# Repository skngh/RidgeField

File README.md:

# Ridge Field

Fully wireless guitar pedal. A small box mounts on the guitar and sends its knobs, joystick and light sensor over Bluetooth to the pedal on the floor, which runs everything and does processing through a Daisy Seed.

**[Full video walking through the pedal!](https://youtu.be/8Uf5aeJEN9k)**

Everything here is free to use!! Please let me know if you make anything with something here, I'd really love to see :)

## Contents

- [`hardware/`](hardware/): KiCad projects for both boards, custom libraries, and ready-to-order PCBWay files
- [`firmware/`](firmware/): all the code
  - [`firmware/daisy/`](firmware/daisy/): the audio DSP running on the Daisy Seed in the pedal
  - [`firmware/ESP32C3/`](firmware/ESP32C3/): the Bluetooth link (guitar-side server and pedal-side client)
- [`enclosure/`](enclosure/): FreeCAD models, STLs, and the Tayda drill template

## How it works

There are two units:

- **Server (on the guitar):** a XIAO ESP32-C3 reads the two knobs, an LDR (light sensor) and a joystick, then sends any changes over BLE. It runs off a Li-ion battery.
- **Main/Client (the pedal):** a second XIAO ESP32-C3 connects to the server and passes the control values to a Daisy Seed over UART. Then the Daisy does all the audio processing.

## Controls

| Control            | What it does                                                             |
| ------------------ | ------------------------------------------------------------------------ |
| Knob 1             | Delay time                                                               |
| Knob 2             | Delay feedback (fully down turns the delay off)                          |
| LDR                | Reverb. Cover it with your hand for more                                 |
| Joystick X         | Pitch shift, an octave up or down depending on direction                 |
| Joystick Y         | Bitcrusher. One direction lowers bit depth, the other lowers sample rate |
| Button press       | Latch the current joystick position                                      |
| Button hold        | LDR calibration, see below                                               |
| Mix knob (pedal)   | Dry/wet                                                                  |
| Footswitch (pedal) | Bypass                                                                   |

**LDR calibration:** hold the joystick button. For the first few seconds leave the LDR uncovered. Once the LED starts blinking fast, cover it and keep holding until the LED goes back to normal (~7 s total). The pedal saves the calibration so it survives next time you unplug and replug.

## Building one

Rough order:

1. **PCBs:** order the 2 pcbs located in [`hardware/PCBWayFiles`](hardware/PCBWayFiles/) (Gerbers, BOM and pick-and-place are all there).
2. **Server Enclosure:** 3D print the parts in [`enclosure/STL files`](enclosure/STL%20files/). Uses [M3x6mm screws](https://www.amazon.com/dp/B0DJQG5YLF?ref_=ppx_hzsearch_conn_dt_b_fed_asin_title_2) and [M3 heat inserts](https://www.amazon.com/dp/B08BCRZZS3).
3. **Main Enclosure:** the main enclosure is a 1590B pedal. I used [Tayda Electronics](https://www.taydaelectronics.com/1590b-style-aluminum-diecast-enclosure.html) for mine so I could order it fully drilled and with a UV print. Here's the [Tayda drill template](enclosure/Tayda_Drill_Schematic.txt).
4. **Firmware:** flash both ESP32-C3s from [`firmware/ESP32C3`](firmware/ESP32C3/), then build and flash the Daisy from [`firmware/daisy`](firmware/daisy/).

See each folder's README for more details.

## The artwork

I got the art on the enclosure UV printed through Tayda. The art isn't included in this repo, but here's how I did it in Blender!

You can attach an image as a background to a camera in Blender. So I took the drill schematic coords and made an illustrator file showing the holes that I added as the background. Then I could easily place objects in the scene and it would line up later with the pedal (for some reason the bluetooth LED on the left didn't line up perfectly, so I think I must've gotten the coords off a tiny bit).

I have a video [here](https://www.youtube.com/watch?v=Ckmy4d0Q_N0&t=555s) showing how to make designs for Tayda's UV printing service.

## Clone it

The DSP library I used is a git submodule, so clone with:

```sh
git clone --recursive https://github.com/skngh/RidgeField.git
# if you already cloned it:
git submodule update --init
```

## Caveats

As I mentioned in the video, I am actually planning on making a V2 of the main pedal PCB going forward. It is fully functioning, but you can hear some of the data transfers as these consistent beeps going, and I'm an idiot who didn't add a LPF to the output buffer, so there's lots of high frequency noise. It's far above the range of human hearing, but I had this issue in the past where some annoying looper pedal folded that range down and caused all this aliasing (at least I think that's what happened), so I plan on making the board 4 layers and then adding a LPF across the output buffer's op amp. Relatively easy, but in order to test I'd have to reorder the boards and I don't really wanna spend that money right now :o

## Built with

- [Daisy Seed](https://electro-smith.com/products/daisy-seed) + [libDaisy](https://github.com/electro-smith/libDaisy) / [DaisySP](https://github.com/electro-smith/DaisySP)
- [Seeed XIAO ESP32-C3](https://wiki.seeedstudio.com/XIAO_ESP32C3_Getting_Started/)
- [NimBLE-Arduino](https://github.com/h2zero/NimBLE-Arduino)
- My [Simple-DSP](https://github.com/skngh/Simple-DSP) library
- KiCad 10.0, FreeCAD 1.1, Blender

## License

[MIT](LICENSE). Do whatever you want with it!

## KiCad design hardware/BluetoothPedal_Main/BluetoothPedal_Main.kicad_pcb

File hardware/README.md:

# Hardware

Made with **KiCad 10.0**. Older versions won't open these files.

- [`BluetoothPedal_Main/`](BluetoothPedal_Main/): the main pedal board. Includes the Daisy, XIAO ESP32-C3, input/output buffers, DC power, footswitch and mix knob.
- [`BluetoothPedal_Server/`](BluetoothPedal_Server/): the guitar-mounted board. XIAO ESP32-C3, MCP3208 ADC, knobs, LDR, joystick, battery.
- [`libs/`](libs/): custom symbols, footprints and 3D models used by both projects
- [`PCBWayFiles/`](PCBWayFiles/): Gerbers, BOM and pick-and-place (`-all-pos.csv`) for each board. If you just want boards, these are all you need.

## Opening the projects

I think both projects should open and look right without any setup? But if you want to edit or update parts you may need to do these steps below:

- **Footprints:** each project has an `fp-lib-table` pointing to `../libs/footprints/Custom_Footprints.pretty`. This originally was an absolute path that I changed, but I'm not totally positive that works so you may need to change it, idk.
- **Symbols:** `custom_symbols` and `Seeed_Studio_XIAO_Series` aren't registered in a project symbol table. If you need them, add `libs/symbols/*.kicad_sym` under _Preferences → Manage Symbol Libraries → Project Specific Libraries_.
- **3D models:** some models seem to be absolute paths from my computer, so you may need to configure them in each footprint's settings.

None of this affects the Gerbers, those should all work fine.

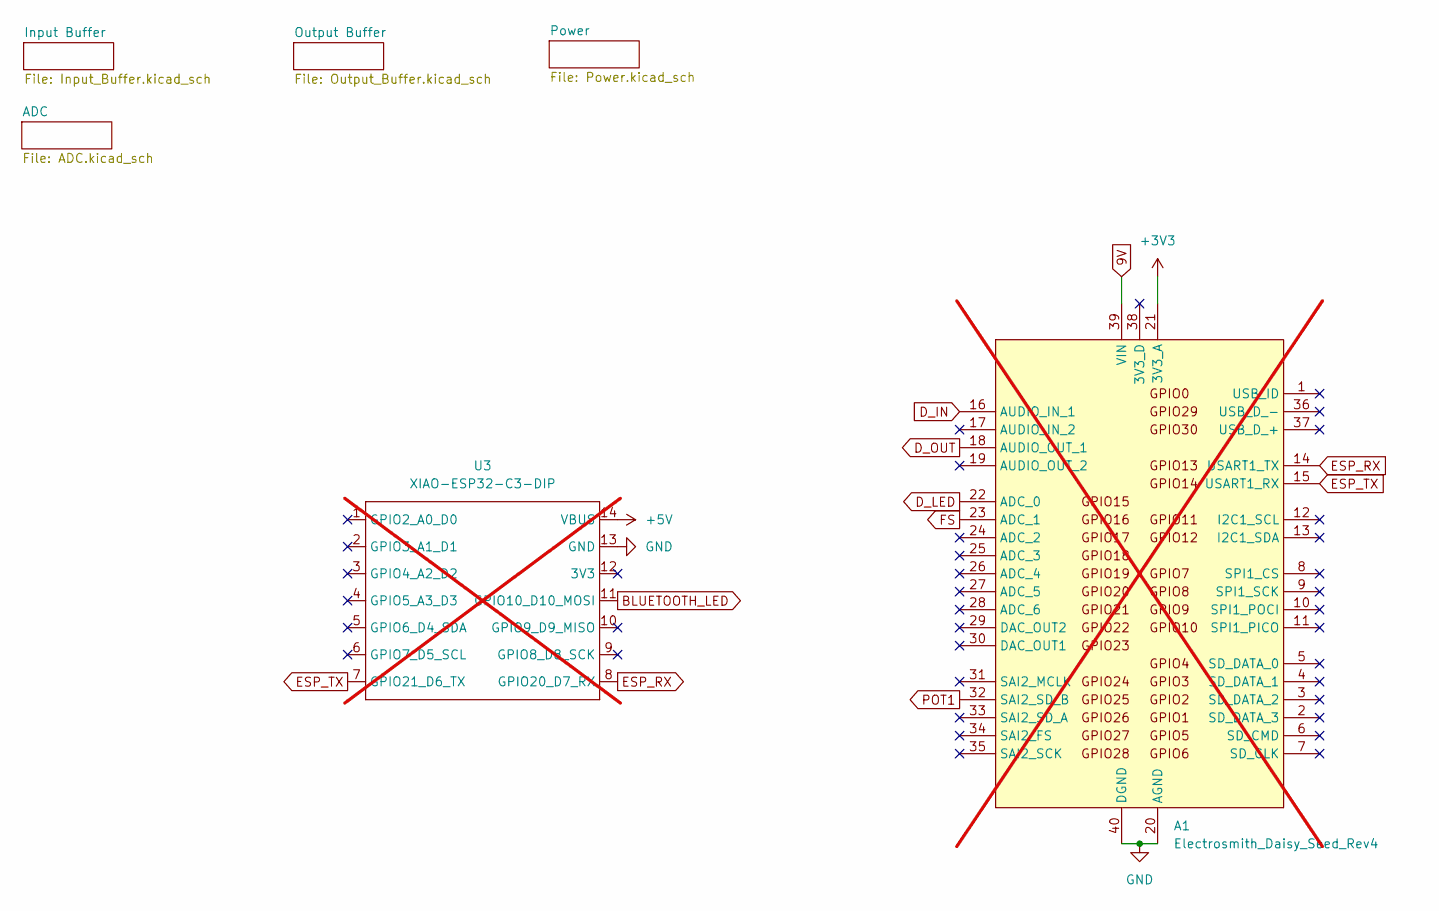
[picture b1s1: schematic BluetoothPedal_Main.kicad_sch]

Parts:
A1: Electrosmith_Daisy_Seed_Rev4; Electrosmith_Daisy_Seed; not fitted
U3: XIAO-ESP32-C3-DIP; not fitted

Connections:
9V: A1.39 (VIN); also elsewhere on the board
+3V3: A1.21 (3V3_A); also elsewhere on the board
+5V: U3.14 (VBUS); also elsewhere on the board
BLUETOOTH_LED: U3.11 (GPIO10_D10_MOSI); also elsewhere on the board
D_IN: A1.16 (AUDIO_IN_1); also elsewhere on the board
D_LED: A1.22 (ADC_0); also elsewhere on the board
D_OUT: A1.18 (AUDIO_OUT_1); also elsewhere on the board
ESP_RX: A1.14 (USART1_TX), U3.8 (GPIO20_D7_RX)
ESP_TX: A1.15 (USART1_RX), U3.7 (GPIO21_D6_TX)
FS: A1.23 (ADC_1); also elsewhere on the board
GND: A1.20 (AGND), A1.40 (DGND), U3.13 (GND); also elsewhere on the board
POT1: A1.32 (SAI2_SD_B); also elsewhere on the board

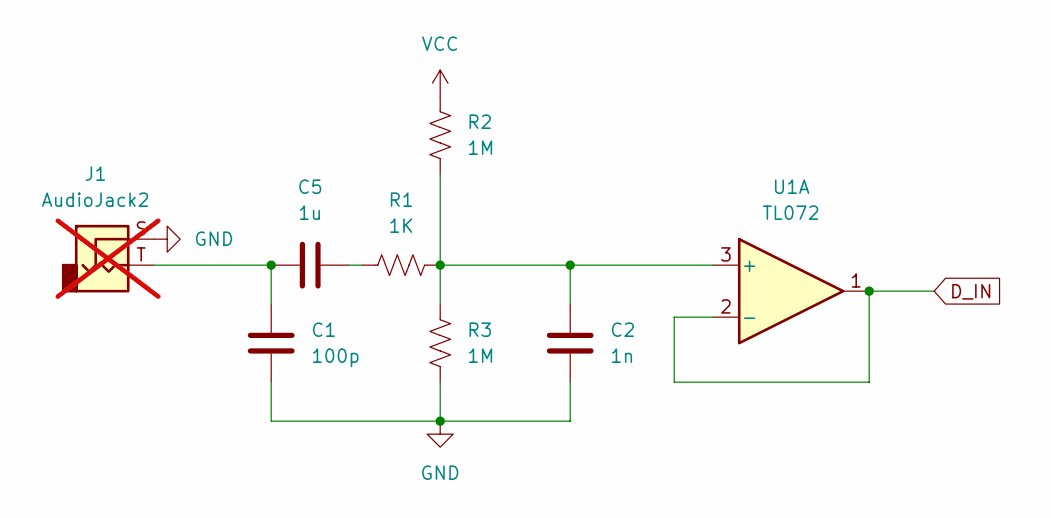
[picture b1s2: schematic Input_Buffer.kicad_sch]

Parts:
C1: 100p; C_0805_2012Metric; MPN CC0805JRNPO9BN101
C2: 1n; C_0805_2012Metric; MPN CC0805JRNPO9BN102
C5: 1u; C_0805_2012Metric; MPN CC0805KKX7R8BB105
J1: AudioJack2; SolderWire-0.5sqmm_1x02_P4.6mm_D0.9mm_OD2.1mm; not fitted
R1: 1K; R_0805_2012Metric; MPN RC0805FR-071KL
R2, R3: 1M; R_0805_2012Metric; MPN RC0805FR-071ML
U1: TL072; SOIC-8_3.9x4.9mm_P1.27mm; MPN TL072CDR

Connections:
D_IN: U1.1, U1.2 (-); also elsewhere on the board
GND: C1.2, C2.2, J1.S, R3.1; also elsewhere on the board
unnamed: C1.1, C5.2, J1.T
unnamed: C5.1, R1.1
unnamed: C2.1, R1.2, R2.1, R3.2, U1.3 (+)
VCC: R2.2; also elsewhere on the board

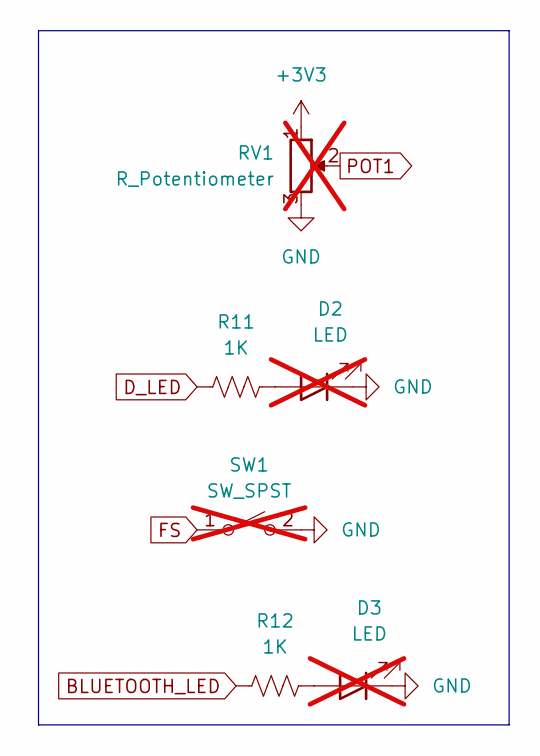
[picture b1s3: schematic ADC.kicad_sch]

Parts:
D2: LED; LED_D5.0mm; not fitted
D3: LED; LED_Rectangular_W5.0mm_H2.0mm; not fitted
R11, R12: 1K; R_0805_2012Metric; MPN RC0805FR-071KL
RV1: R_Potentiometer; RV11114NO; not fitted
SW1: SW_SPST; SolderWire-0.5sqmm_1x02_P4.6mm_D0.9mm_OD2.1mm; not fitted

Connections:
+3V3: RV1.1; also elsewhere on the board
BLUETOOTH_LED: R12.1; also elsewhere on the board
D_LED: R11.1; also elsewhere on the board
FS: SW1.1 (A); also elsewhere on the board
GND: D2.1 (K), D3.1 (K), RV1.3, SW1.2 (B); also elsewhere on the board
unnamed: D2.2 (A), R11.2
unnamed: D3.2 (A), R12.2
POT1: RV1.2; also elsewhere on the board

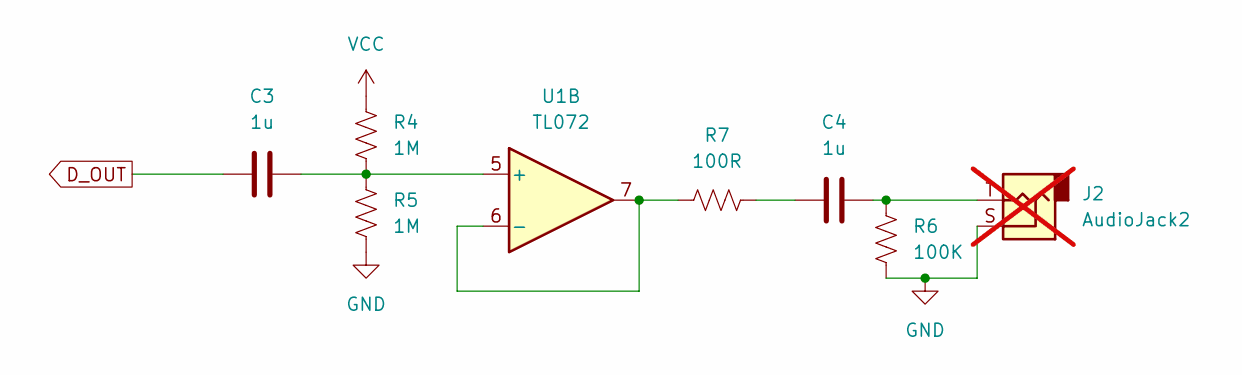
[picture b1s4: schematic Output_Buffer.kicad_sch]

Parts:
C3, C4: 1u; C_0805_2012Metric; MPN CC0805KKX7R8BB105
J2: AudioJack2; SolderWire-0.5sqmm_1x02_P4.6mm_D0.9mm_OD2.1mm; not fitted
R4, R5: 1M; R_0805_2012Metric; MPN RC0805FR-071ML
R6: 100K; R_0805_2012Metric; MPN RC0805FR-07100KL
R7: 100R; R_0805_2012Metric; MPN RC0805FR-07100RL
U1: TL072; SOIC-8_3.9x4.9mm_P1.27mm; MPN TL072CDR

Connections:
D_OUT: C3.1; also elsewhere on the board
GND: J2.S, R5.2, R6.2; also elsewhere on the board
unnamed: C4.1, R7.2
unnamed: C4.2, J2.T, R6.1
unnamed: C3.2, R4.2, R5.1, U1.5 (+)
unnamed: R7.1, U1.6 (-), U1.7
VCC: R4.1; also elsewhere on the board

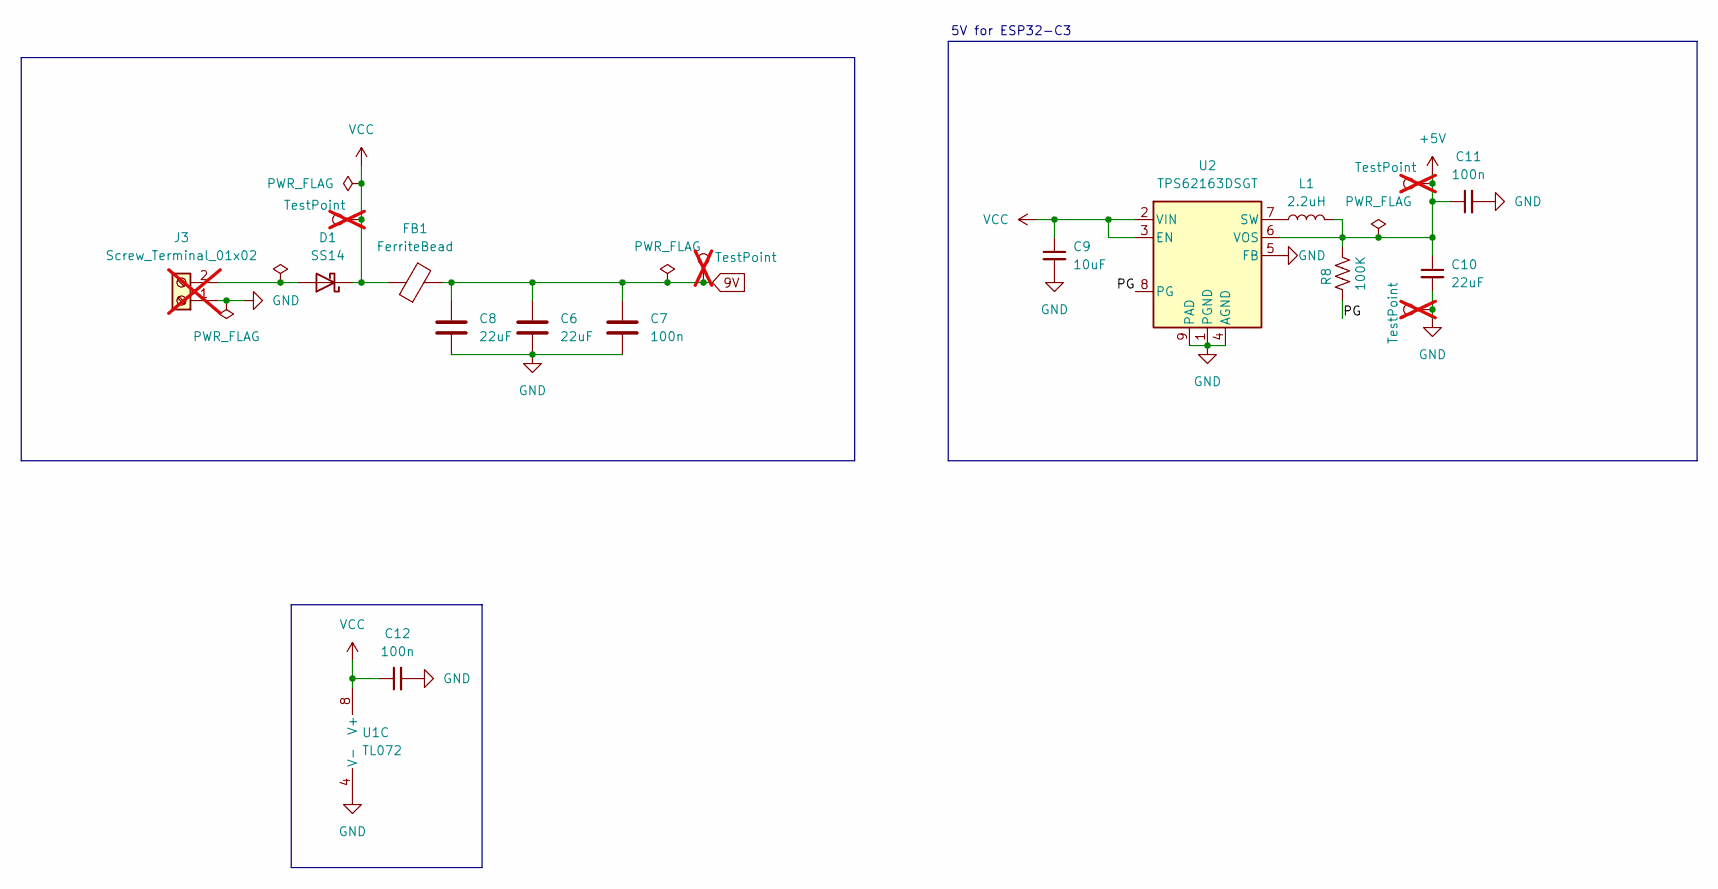
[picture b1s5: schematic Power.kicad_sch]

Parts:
C6, C8, C10: 22uF; C_0805_2012Metric; MPN CC0805MKX5R8BB226
C7, C11, C12: 100n; C_0805_2012Metric; MPN C0805C104K5RACTU
C9: 10uF; C_0805_2012Metric; MPN CC0805KKX5R8BB106
D1: SS14; D_SMA; MPN SS14
FB1: FerriteBead; L_0805_2012Metric; MPN BLM21PG600SN1D
J3: Screw_Terminal_01x02; Screw Terminal 1x2 5mm; not fitted
L1: 2.2uH; Coilcraft_XFL3012; MPN XFL3012-222MEC
R8: 100K; R_0805_2012Metric; MPN RC0805FR-07100KL
TP1, TP2, TP3, TP4: TestPoint; TestPoint_Pad_D2.0mm; not fitted
U1: TL072; SOIC-8_3.9x4.9mm_P1.27mm; MPN TL072CDR
U2: TPS62163DSGT; WSON-8-1EP_2x2mm_P0.5mm_EP0.9x1.6mm_ThermalVias; MPN TPS62163DSGT

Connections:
9V: C6.1, C7.1, C8.1, FB1.2, TP2.1 (1_1); also elsewhere on the board
+5V: C10.1, C11.1, L1.2, R8.2, TP1.1 (1_1), U2.6 (VOS); also elsewhere on the board
/Power/PG: R8.1, U2.8 (PG)
GND: C6.2, C7.2, C8.2, C9.2, C10.2, C11.2, C12.2, J3.1, TP4.1 (1_1), U1.4 (V-), U2.1 (PGND), U2.4 (AGND), U2.5 (FB), U2.9 (PAD); also elsewhere on the board
unnamed: D1.2 (A), J3.2
unnamed: L1.1, U2.7 (SW)
VCC: C9.1, C12.1, D1.1 (K), FB1.1, TP3.1 (1_1), U1.8 (V+), U2.2 (VIN), U2.3 (EN); also elsewhere on the board

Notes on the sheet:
5V for ESP32-C3

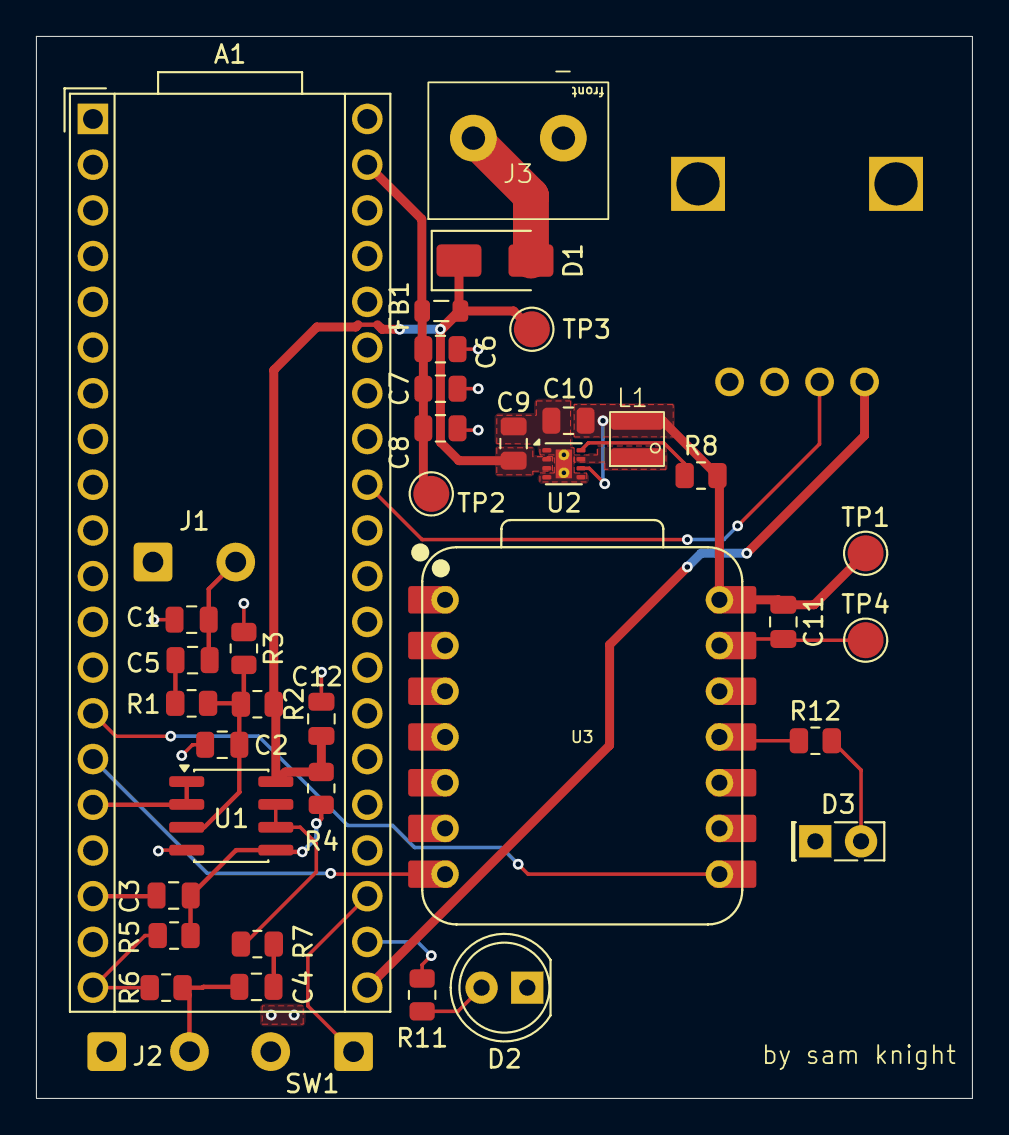
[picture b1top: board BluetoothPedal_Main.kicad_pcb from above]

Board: 2 copper layers, 52.0 x 59.0 mm, 40 parts (1 on the bottom side), 25 nets.

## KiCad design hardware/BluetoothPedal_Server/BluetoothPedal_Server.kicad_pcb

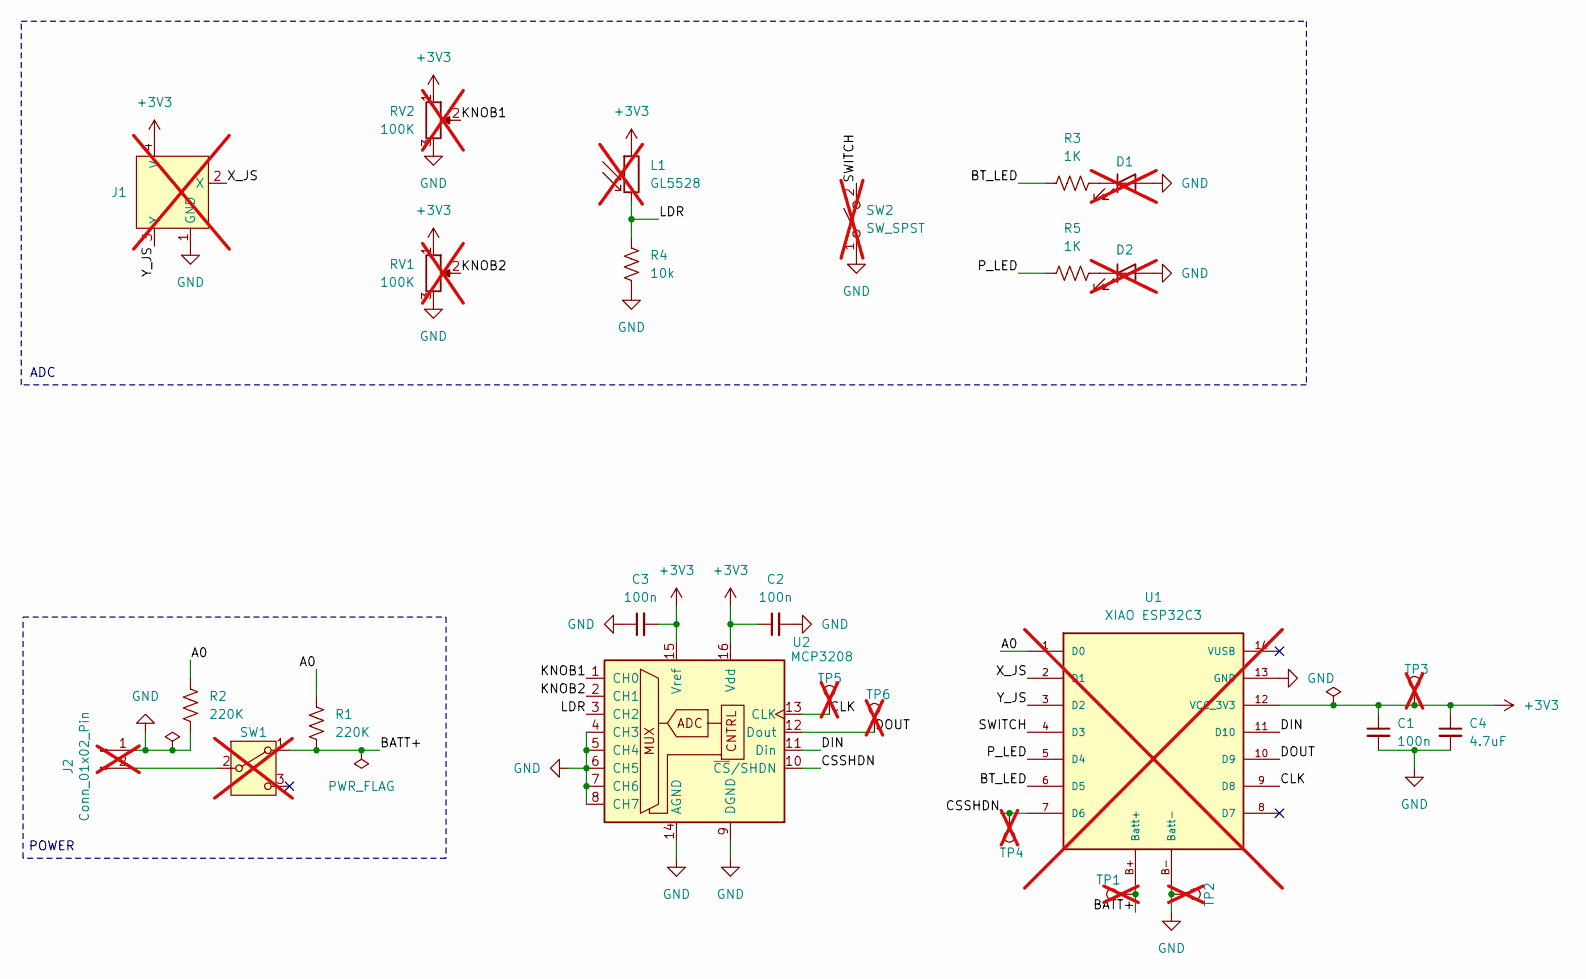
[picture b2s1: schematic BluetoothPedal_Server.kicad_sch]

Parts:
C1, C2, C3: 100n; C_0805_2012Metric; MPN GCM21BR71H104KA37L
C4: 4.7uF; C_0805_2012Metric; MPN GRM219R61A475KE19D
D1: LED_D3.0mm; not fitted
D2: LED_Rectangular_W5.0mm_H2.0mm; not fitted
J1: Mini 2-Axis Analog Thumbstick; not fitted
J2: Conn_01x02_Pin; JST_PH_S2B-PH-K_1x02_P2.00mm_Horizontal; not fitted
L1: GL5528; R_LDR_5.1x4.3mm_P3.4mm_Vertical; not fitted
R1, R2: 220K; R_0805_2012Metric; MPN RC0805FR-07220KL
R3, R5: 1K; R_0805_2012Metric; MPN RC0805FR-071KL
R4: 10k; R_0805_2012Metric; MPN RC0805FR-0710KL
RV1, RV2: 100K; RV11114NO; not fitted
SW1: SW_SPDT; Slide Switch 1P2T; not fitted
SW2: SW_SPST; SolderWire-0.5sqmm_1x02_P4.8mm_D0.9mm_OD2.3mm; not fitted
TP1, TP2, TP3, TP4, TP5, TP6: TestPoint; TestPoint_Pad_D2.0mm; not fitted
U1: XIAO ESP32C3; xiao_esp32c3; not fitted
U2: MCP3208; SOIC-16_3.9x9.9mm_P1.27mm; MPN MCP3208-CI/SL

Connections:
+3V3: C1.1, C2.1, C3.2, C4.1, J1.4 (V), L1.1, RV1.1, RV2.1, TP3.1 (1_1), U1.12 (VCC_3V3), U2.15 (Vref), U2.16 (Vdd)
/A0: R1.2, R2.1, U1.1 (D0)
/BATT+: R1.1, SW1.1 (A), TP1.1 (1_1), U1.B+ (Batt+)
/BT_LED: R3.1, U1.6 (D5)
/CLK: TP5.1 (1_1), U1.9 (D8), U2.13 (CLK)
/CSSHDN: TP4.1 (1_1), U1.7 (D6), U2.10 (~CS/SHDN)
/DIN: U1.11 (D10), U2.11 (Din)
/DOUT: TP6.1 (1_1), U1.10 (D9), U2.12 (Dout)
/KNOB1: RV2.2, U2.1 (CH0)
/KNOB2: RV1.2, U2.2 (CH1)
/LDR: L1.2, R4.1, U2.3 (CH2)
/P_LED: R5.1, U1.5 (D4)
/SWITCH: SW2.2 (B), U1.4 (D3)
/X_JS: J1.2 (X), U1.2 (D1)
/Y_JS: J1.3 (Y), U1.3 (D2)
GND: C1.2, C2.2, C3.1, C4.2, D1.2 (A), D2.2 (A), J1.1 (GND), J2.1, R2.2, R4.2, RV1.3, RV2.3, SW2.1 (A), TP2.1 (1_1), U1.13 (GND), U1.B- (Batt-), U2.4 (CH3), U2.5 (CH4), U2.6 (CH5), U2.7 (CH6), U2.8 (CH7), U2.9 (DGND), U2.14 (AGND)
unnamed: D1.1 (K), R3.2
unnamed: D2.1 (K), R5.2
unnamed: J2.2, SW1.2 (B)

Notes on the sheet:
POWER
ADC

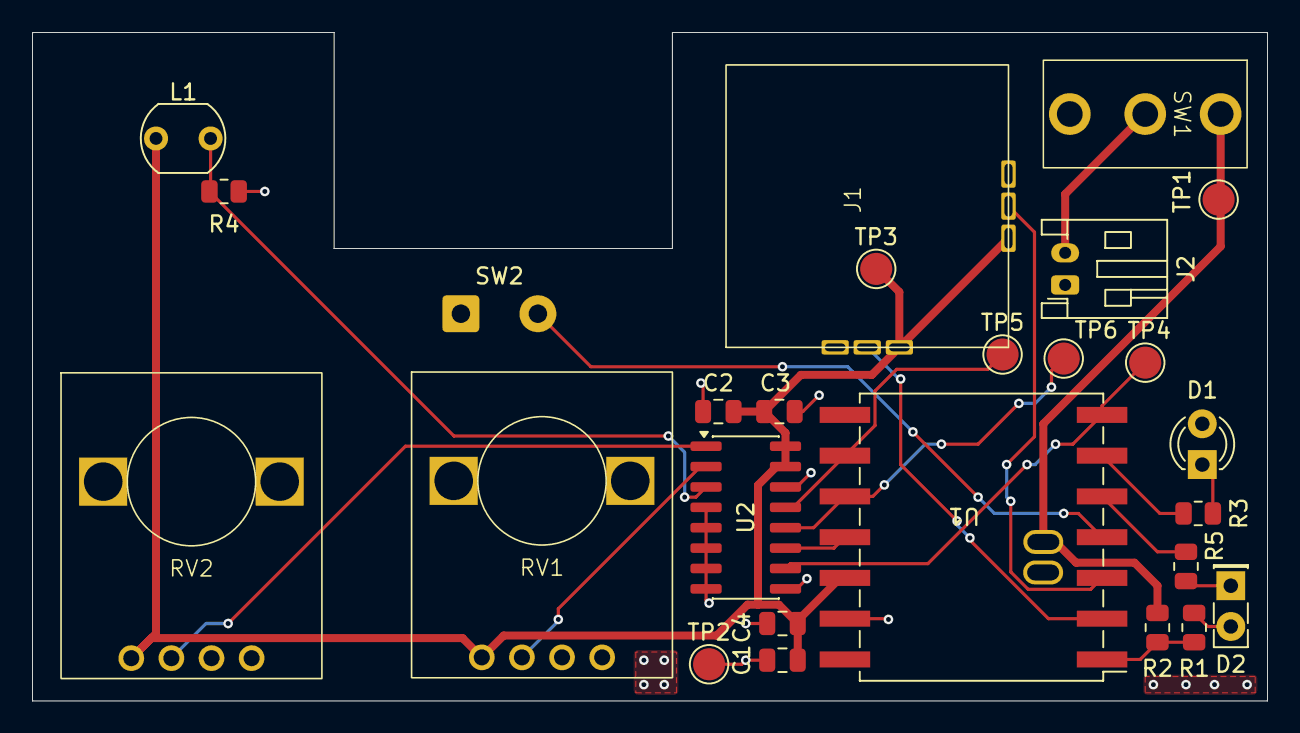
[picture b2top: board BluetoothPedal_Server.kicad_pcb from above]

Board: 2 copper layers, 77.0 x 41.7 mm, 26 parts (0 on the bottom side), 19 nets.

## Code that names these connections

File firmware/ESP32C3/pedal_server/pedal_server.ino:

// BLE server — runs on the guitar/handheld unit (XIAO ESP32-C3)
// Reads the controls and notifies the connected client on change.
//
// Control sources:
//   Knob1 / Knob2 / LDR  -> MCP3208 external ADC (CH0 / CH1 / CH2) over SPI
//   Joystick X / Y       -> XIAO on-board ADC (D1 / D2)
//   Switch               -> joystick push-button (D3, digital, active-low)
//
// Pin map (XIAO ESP32-C3, server side):
//   D0  / GPIO2   A0           battery sense (via divider — see BATT_* below)
//   D1  / GPIO3   Joystick X   (ADC)
//   D2  / GPIO4   Joystick Y   (ADC)
//   D3  / GPIO5   Switch       (digital, INPUT_PULLUP)
//   D4  / GPIO6   BT_LED       connection status (blinks advertising, solid connected)
//   D5  / GPIO7   P_LED        battery status (brightness = %, blinks when low)
//   D6  / GPIO21  CS/SHDN      MCP3208 chip select
//   D8  / GPIO8   SCK          MCP3208 CLK
//   D9  / GPIO9   MISO         MCP3208 Dout
//   D10 / GPIO10  MOSI         MCP3208 Din

#include <NimBLEDevice.h>
#include <SPI.h>
#include "esp_system.h" 

// ── MCP3208 SPI pins ──────────────────────────────────────
static const uint8_t PIN_SCK  = D8;
static const uint8_t PIN_MISO = D9;
static const uint8_t PIN_MOSI = D10;
static const uint8_t PIN_CS   = D6;

static const uint32_t MCP_SPI_HZ = 1000000;

// ── Status LEDs ───────────────────────────────────────────
static const uint8_t BATT_LED_PIN = D5;   // battery status
static const uint8_t CONN_LED_PIN = D4;   // client connected

// ── Battery sense (R1/R2 = 220k/220k divider into A0) ─────
static const uint8_t BATT_ADC_PIN = D0;
static const float   BATT_DIVIDER = 2.0f;   // (R1 + R2) / R2 = (220k + 220k) / 220k
static const float   BATT_FULL_V  = 4.20f;  // 1S Li-Ion full  -> 100%
static const float   BATT_EMPTY_V = 3.30f;  // 1S Li-Ion empty -> 0%
static const float   BATT_LOW_V   = 3.45f;  // below this: blink instead of dim

// ── Control definitions ───────────────────────────────────
enum Source { SRC_MCP, SRC_ADC, SRC_DIGITAL };

struct Control {
    const char*           name;
    Source                source;
    uint8_t               channel;   // MCP channel for SRC_MCP, else GPIO pin
    const char*           uuid;
    NimBLECharacteristic* characteristic;
    uint16_t              lastValue;
};

static Control controls[] = {
    { "Knob1",  SRC_MCP,     0,  "a1b2c3d4-0001-0000-0000-000000000001", nullptr, 0 },
    { "Knob2",  SRC_MCP,     1,  "a1b2c3d4-0001-0000-0000-000000000002", nullptr, 0 },
    { "LDR",    SRC_MCP,     2,  "a1b2c3d4-0001-0000-0000-000000000003", nullptr, 0 },
    { "JoyX",   SRC_ADC,     D1, "a1b2c3d4-0001-0000-0000-000000000004", nullptr, 0 },
    { "JoyY",   SRC_ADC,     D2, "a1b2c3d4-0001-0000-0000-000000000005", nullptr, 0 },
    { "Switch", SRC_DIGITAL, D3, "a1b2c3d4-0001-0000-0000-000000000006", nullptr, 0 },
};
static const uint8_t NUM_CONTROLS = sizeof(controls) / sizeof(controls[0]);

// ── BLE config ────────────────────────────────────────────
static const char* SERVICE_UUID = "a1b2c3d4-0001-0000-0000-000000000000";
static const char* DEVICE_NAME  = "Pedal";

// ── Tuning ────────────────────────────────────────────────
static const uint16_t ADC_DEADBAND = 12;  // ignore analog noise smaller than this (0–4095)
static const uint32_t SAMPLE_MS    = 20;  // 50 Hz sample rate

// ── State ─────────────────────────────────────────────────
static NimBLEServer* bleServer = nullptr;
static bool          clientConnected = false;

// ── MCP3208 single-ended read (12-bit, 0–4095) ────────────
uint16_t readMCP3208(uint8_t channel) {
    SPI.beginTransaction(SPISettings(MCP_SPI_HZ, MSBFIRST, SPI_MODE0));
    digitalWrite(PIN_CS, LOW);
    uint8_t cmd = 0b00000110 | ((channel & 0x04) >> 2); 
    SPI.transfer(cmd);
    uint8_t hi = SPI.transfer((channel & 0x03) << 6);   
    uint8_t lo = SPI.transfer(0x00);
    digitalWrite(PIN_CS, HIGH);
    SPI.endTransaction();
    return ((hi & 0x0F) << 8) | lo;
}

uint16_t readControl(const Control& c) {
    switch (c.source) {
        case SRC_MCP:     return readMCP3208(c.channel);
        case SRC_ADC:     return analogRead(c.channel);        
        case SRC_DIGITAL: return digitalRead(c.channel) ? 0 : 1;
    }
    return 0;
}

static float readBatteryVolts() {
    return (analogReadMilliVolts(BATT_ADC_PIN) / 1000.0f) * BATT_DIVIDER;
}

static int batteryPercent(float volts) {
    int pct = (int)((volts - BATT_EMPTY_V) / (BATT_FULL_V - BATT_EMPTY_V) * 100.0f);
    return constrain(pct, 0, 100);
}

// ── Battery status LED ────────────────────────────────────
// Brightness tracks battery
void updateBatteryLed() {
    static uint32_t lastCheck = 0;
    static float    volts     = BATT_FULL_V;

    if (millis() - lastCheck > 1000) {
        lastCheck = millis();
        volts = readBatteryVolts();
        Serial.printf("Battery: %.2f V (%d%%)%s\n",
                      volts, batteryPercent(volts), volts < BATT_LOW_V ? " LOW" : "");
    }

    if (volts < BATT_LOW_V)
        analogWrite(BATT_LED_PIN, ((millis() / 250) % 2) ? 255 : 0);  // blink ~2 Hz
    else
        analogWrite(BATT_LED_PIN, map(batteryPercent(volts), 0, 100, 0, 255));
}

// Connection LED: solid when a client is connected, blinks ~2 Hz while advertising.
void updateConnLed() {
    digitalWrite(CONN_LED_PIN, clientConnected ? HIGH : ((millis() / 250) % 2));
}

// ── BLE callbacks ─────────────────────────────────────────
class ServerCallbacks : public NimBLEServerCallbacks {
    void onConnect(NimBLEServer*, NimBLEConnInfo&) override {
        clientConnected = true;   // LED handling is in updateConnLed()
        Serial.println("Client connected");
    }
    void onDisconnect(NimBLEServer*, NimBLEConnInfo&, int) override {
        clientConnected = false;
        Serial.println("Client disconnected — restarting advertising");
        NimBLEDevice::startAdvertising();
    }
};

void bootBlink() {
    for (int i = 0; i < 3; i++) {
        digitalWrite(BATT_LED_PIN, HIGH);
        digitalWrite(CONN_LED_PIN, HIGH);
        delay(120);
        digitalWrite(BATT_LED_PIN, LOW);
        digitalWrite(CONN_LED_PIN, LOW);
        delay(120);
    }
}

void setup() {
    Serial.begin(115200);
    delay(300);
    Serial.printf("\n=== Pedal server boot === reset_reason=%d %s\n",
                  esp_reset_reason(),
                  esp_reset_reason() == ESP_RST_BROWNOUT ? "(BROWNOUT! supply sagging)" : "");

    pinMode(BATT_LED_PIN, OUTPUT);
    pinMode(CONN_LED_PIN, OUTPUT);
    digitalWrite(BATT_LED_PIN, LOW);
    digitalWrite(CONN_LED_PIN, LOW);
    bootBlink(); 

    // Control inputs
    for (auto& c : controls) {
        if (c.source == SRC_ADC)          pinMode(c.channel, INPUT);
        else if (c.source == SRC_DIGITAL) pinMode(c.channel, INPUT_PULLUP);
    }

    // MCP3208 SPI
    pinMode(PIN_CS, OUTPUT);
    digitalWrite(PIN_CS, HIGH);
    SPI.begin(PIN_SCK, PIN_MISO, PIN_MOSI, PIN_CS);
    Serial.println("[1] GPIO + SPI ready");

    Serial.printf("[2] Battery (pre-BLE): %.2f V\n", readBatteryVolts());

    Serial.println("[3] starting BLE radio...");
    NimBLEDevice::init(DEVICE_NAME);
    bleServer = NimBLEDevice::createServer();
    bleServer->setCallbacks(new ServerCallbacks());

    NimBLEService* service = bleServer->createService(SERVICE_UUID);

    for (auto& c : controls) {
        c.characteristic = service->createCharacteristic(
            c.uuid,
            NIMBLE_PROPERTY::READ | NIMBLE_PROPERTY::NOTIFY
        );
        uint16_t initial = readControl(c);
        c.characteristic->setValue(initial);
        c.lastValue = initial;
    }

    service->start();

    NimBLEAdvertising* adv = NimBLEDevice::getAdvertising();
    adv->addServiceUUID(SERVICE_UUID);
    adv->setName(DEVICE_NAME);       
    adv->enableScanResponse(true); 
    bool advOk = adv->start();

    Serial.printf("[4] Advertising as \"%s\" with %u control(s) — start=%s\n",
                  DEVICE_NAME, NUM_CONTROLS, advOk ? "OK" : "FAILED");
}

void loop() {
    updateBatteryLed();
    updateConnLed();

    static uint32_t lastSample = 0;
    if (millis() - lastSample < SAMPLE_MS) return;
    lastSample = millis();

    for (auto& c : controls) {
        uint16_t val = readControl(c);

        bool changed = (c.source == SRC_DIGITAL)
                           ? (val != c.lastValue)
                           : (abs((int)val - (int)c.lastValue) > ADC_DEADBAND);
        if (!changed) continue;

        c.lastValue = val;
        c.characteristic->setValue(val);
        if (clientConnected) {
            c.characteristic->notify();
        }
        // Serial.printf("%s: %u\n", c.name, val);
    }
}

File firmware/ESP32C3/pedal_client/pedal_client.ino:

// BLE client — runs on the pedalboard unit (XIAO ESP32-C3)
// Scans for the guitar/server, connects, subscribes to every control,
// and forwards a combined snapshot to the Daisy Seed over UART.
//
// Wiring (client side):
//   D6  / GPIO21  ESP_TX        -> Daisy USART1_RX (pin 15)
//   D7  / GPIO20  ESP_RX        <- Daisy USART1_TX (pin 14)
//   D10 / GPIO10  BLUETOOTH_LED -> on while connected to the server
//   shared GND between the ESP32 and the Daisy Seed

#include <NimBLEDevice.h>

// ── UART link to the Daisy Seed ───────────────────────────
static const uint8_t  UART_TX_PIN = D6;   // GPIO21 -> Daisy RX
static const uint8_t  UART_RX_PIN = D7;   // GPIO20 <- Daisy TX
static const uint32_t UART_BAUD   = 115200;
#define DaisySerial Serial1

// ── Connection-status LED ─────────────────────────────────
static const uint8_t  LED_PIN = D10;      // on = connected to server

// ── Match SERVICE_UUID, DEVICE_NAME and characteristic UUIDs to the server ──
static const char* SERVICE_UUID = "a1b2c3d4-0001-0000-0000-000000000000";
static const char* DEVICE_NAME  = "Pedal";

// Order here defines the index used in the UART packet below.
enum ControlIndex { KNOB1, KNOB2, LDR, JOY_X, JOY_Y, SWITCH, NUM_CONTROLS };

struct Control {
    const char*                 name;
    const char*                 uuid;
    NimBLERemoteCharacteristic* characteristic;
};

static Control controls[NUM_CONTROLS] = {
    { "Knob1",  "a1b2c3d4-0001-0000-0000-000000000001", nullptr },
    { "Knob2",  "a1b2c3d4-0001-0000-0000-000000000002", nullptr },
    { "LDR",    "a1b2c3d4-0001-0000-0000-000000000003", nullptr },
    { "JoyX",   "a1b2c3d4-0001-0000-0000-000000000004", nullptr },
    { "JoyY",   "a1b2c3d4-0001-0000-0000-000000000005", nullptr },
    { "Switch", "a1b2c3d4-0001-0000-0000-000000000006", nullptr },
};

// Latest value per control: 0–4095 for the analog inputs, 0/1 for the switch.
static volatile uint16_t values[NUM_CONTROLS] = { 0 };
static volatile bool     dirty = false;   // a value changed and needs forwarding

// ── State ─────────────────────────────────────────────────
static NimBLEClient*  bleClient = nullptr;
static NimBLEAddress  serverAddress;
static bool           connected = false;
static bool           doConnect = false;

// ── UART packet to the Daisy ──────────────────────────────
// Fixed 14-byte frame, sent whenever any control changes:
//   [0]      0xAA   sync
//   [1]      0x55   sync
//   [2..3]   Knob1  uint16 little-endian
//   [4..5]   Knob2
//   [6..7]   LDR
//   [8..9]   JoyX
//   [10..11] JoyY
//   [12]     Switch (0/1)
//   [13]     checksum = XOR of bytes [2..12]
void sendToDaisy() {
    uint8_t pkt[14];
    pkt[0] = 0xAA;
    pkt[1] = 0x55;
    for (int i = 0; i < 5; i++) {
        uint16_t v = values[i];
        pkt[2 + i * 2] = v & 0xFF;
        pkt[3 + i * 2] = v >> 8;
    }
    pkt[12] = values[SWITCH] ? 1 : 0;
    uint8_t cksum = 0;
    for (int i = 2; i <= 12; i++) cksum ^= pkt[i];
    pkt[13] = cksum;
    DaisySerial.write(pkt, sizeof(pkt));
}

// ── Notification callback ─────────────────────────────────
void notifyCallback(NimBLERemoteCharacteristic* pChar, uint8_t* pData, size_t length, bool isNotify) {
    if (length < 2) return;
    uint16_t raw = pData[0] | (pData[1] << 8);

    for (int i = 0; i < NUM_CONTROLS; i++) {
        if (controls[i].characteristic == pChar) {
            values[i] = raw;
            dirty = true;
            break;
        }
    }
}

// ── BLE callbacks ─────────────────────────────────────────
class ClientCallbacks : public NimBLEClientCallbacks {
    void onConnect(NimBLEClient*) override {
        Serial.println("Connected to server");
    }
    void onDisconnect(NimBLEClient*, int reason) override {
        connected = false;
        Serial.printf("Disconnected (reason %d) — scanning again\n", reason);
        NimBLEDevice::getScan()->start(0);
    }
};

class ScanCallbacks : public NimBLEScanCallbacks {
    void onResult(const NimBLEAdvertisedDevice* device) override {
        std::string name = device->getName();
        bool        bySvc  = device->isAdvertisingService(NimBLEUUID(SERVICE_UUID));
        bool        byName = (name == DEVICE_NAME);

        if (!name.empty() || bySvc) {
            Serial.printf("Saw %s  name='%s'  svc=%d\n",
                          device->getAddress().toString().c_str(), name.c_str(), bySvc);
        }

        if (bySvc || byName) {
            Serial.printf("Found server: %s\n", device->getAddress().toString().c_str());
            NimBLEDevice::getScan()->stop();
            serverAddress = device->getAddress();
            doConnect = true;
        }
    }
};

// ── Connection logic ──────────────────────────────────────
bool connectToServer() {
    bleClient = NimBLEDevice::createClient();
    bleClient->setClientCallbacks(new ClientCallbacks());

    if (!bleClient->connect(serverAddress)) {
        Serial.println("Connection failed");
        NimBLEDevice::deleteClient(bleClient);
        bleClient = nullptr;
        return false;
    }

    NimBLERemoteService* service = bleClient->getService(SERVICE_UUID);
    if (!service) {
        Serial.println("Service not found on server");
        bleClient->disconnect();
        return false;
    }

    for (int i = 0; i < NUM_CONTROLS; i++) {
        Control& c = controls[i];
        c.characteristic = service->getCharacteristic(c.uuid);
        if (!c.characteristic) {
            Serial.printf("Characteristic not found: %s\n", c.name);
            continue;
        }

        if (c.characteristic->canRead()) {
            values[i] = c.characteristic->readValue<uint16_t>();
        }

        if (c.characteristic->canNotify()) {
            c.characteristic->subscribe(true, notifyCallback);
        }
    }

    connected = true;       
    dirty = true;          
    return true;
}

// Connection LED: solid when connected, blinks ~2 Hz while scanning/connecting.
void updateConnLed() {
    digitalWrite(LED_PIN, connected ? HIGH : ((millis() / 250) % 2));
}

// ── Arduino entry points ──────────────────────────────────
void setup() {
    Serial.begin(115200);
    DaisySerial.begin(UART_BAUD, SERIAL_8N1, UART_RX_PIN, UART_TX_PIN);

    pinMode(LED_PIN, OUTPUT);
    digitalWrite(LED_PIN, LOW);

    NimBLEDevice::init("");
    NimBLEScan* scan = NimBLEDevice::getScan();
    scan->setScanCallbacks(new ScanCallbacks());
    scan->setActiveScan(true);
    scan->start(0);  // scan indefinitely until the server is found

    Serial.println("Scanning for server...");
}

void loop() {
    updateConnLed();

    if (doConnect) {
        doConnect = false;
        if (connectToServer()) {
            Serial.println("Subscribed — ready");
        } else {
            NimBLEDevice::getScan()->start(0);
        }
    }

    if (dirty) {
        dirty = false;
        sendToDaisy();
    }

    static uint32_t lastPrint = 0;
    if (connected && millis() - lastPrint > 500) {
        lastPrint = millis();
        Serial.printf("K1=%u K2=%u LDR=%u JX=%u JY=%u SW=%u\n",
                      values[KNOB1], values[KNOB2], values[LDR],
                      values[JOY_X], values[JOY_Y], values[SWITCH]);
    }
}
